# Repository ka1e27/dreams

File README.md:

# D.R.E.A.M.S

Autonomous survey catamaran: CV-based obstacle avoidance, environmental sensing, and cellular
telemetry to a web dashboard.

**Website:** https://ka1e27.github.io/dreams/ (the boat, the build log and weekly updates). Its source is in [`website/`](website/).
**Instagram:** [@dreams.boat.project](https://www.instagram.com/dreams.boat.project/).

## Status: V3, starting from scratch

V3 is a ground-up rebuild on new hardware. The carrier PCB is designed and fully routed. **None of
the software has been written yet.** This repo is the clean base it will be written on.

The V2 boat is archived, not deleted. The whole V2 stack is frozen at the tag
[`v2-final`](../../tree/v2-final): RP2040 firmware, the Pi 5 navigation and CV code, the
dashboards, the cloud pipeline, and the V2 board with its docs.

**Start with [`docs/v3/V3_DESIGN_BRIEF.md`](docs/v3/V3_DESIGN_BRIEF.md)** for the locked
decisions, the current budget, part choices with their reasons, and the layout traps the first
attempt hit.

## The boards

| Board | Folder | What it is |
|---|---|---|
| **V3 carrier** (rev F) | [`Boat_PCB/Boat_PCB_V3/`](Boat_PCB/Boat_PCB_V3/) | The main board: Pi 5 and two Pico 2s, running from 10S Li-ion. 122.1 × 95.5 mm, 4 layers (JLC04161H-7628, 1 oz outer / 0.5 oz inner, ENIG), 140 footprints, fully routed |
| **V3.1 starter carrier** (2026-10-10) | [`Boat_PCB/Boat_PCB_V3_1/`](Boat_PCB/Boat_PCB_V3_1/) | An interim board to get the boat moving before the full carrier. It keeps the Pi 5 and the 5 V buck, uses one Raspberry Pi Pico 2 instead of the full board's two, and runs from one 10S Li-ion pack. CAN chain for the VESCs, RC input, GPS, an on-board SHT41, a Qwiic port for the TMP119, hull leak probes, ESC headers and the pod tether, on a 98 × 67 mm 2-layer board. See [`docs/v3/V3_1_STARTER_CARRIER.md`](docs/v3/V3_1_STARTER_CARRIER.md) |
| **Pod** | [`Boat_PCB/Pod_PCB_V3/`](Boat_PCB/Pod_PCB_V3/) | A Seeed XIAO ESP32-S3 on its own board, on the winch tether |
| Shared library | [`Boat_PCB/lib/`](Boat_PCB/lib/) | The `dreams_v3` KiCad library all three boards use |

**Power on the V3 carrier (rev F):** two 10S 10 Ah Li-ion packs in parallel make one 10S bus.

- **Drive:** the 10S bus straight to the VESCs, off-board; the carrier only senses its voltage.
- **Electronics:** 10S → 5 V buck → Pi and both Picos. An optional 4S backup on J18 keeps that 5 V
  side up while the 10S bus is off. A 15 V regulator (U15) feeds the stepper driver and the pod.
- **Winch:** 10S → P-FET kill → ESC.

Pack fusing is off-board. On the board, PTCs guard the pod feed (F1) and the LED and SBUS 5 V
outputs (F2, F3).

## Architecture

```
Raspberry Pi 5 ─ navigation, mission logic, CV, cloud link        Python (not yet written)
  │ UART on the GPIO header to Pico A, plus a reset line to each Pico
  ├─ Pico A (Pico 2) ─ control                                    C++ (not yet written)
  │    ├─ CAN via TJA1051T/3 ─► VESC ×2 (node IDs 1, 2) for drive, on the PIO (can2040)
  │    ├─ UART ─────────────► SBUS RC receiver
  │    ├─ PWM ──────────────► winch ESC, behind a fail-safe-OFF high-side P-FET kill
  │    ├─ STEP/DIR ─────────► A4988 radar-bar stepper
  │    └─ GPIO / ADC ───────► WS2812 status LED · hull leak L/R · 10S pack divider
  └─ Pico B (Pico 2) ─ sensors                                    C++ (not yet written)
       ├─ I²C via TCA9548A ─► SHT45 ×2, BNO085, ADXL375, BH1750, INA228 ×2
       └─ UART ─────────────► GPS (M10-25Q) · pod tether (RS-485)
```

- **The Picos** sit in sockets under the carrier, with a UART link between them. They replaced the
  Teensy 4.1 in rev E (2026-10-13).
- **The Pi** talks to Pico A over a UART on its GPIO header, and Pico B reaches the Pi through Pico A.
  So USB cables are optional: without them the Pi's USB ports stay free for cameras and the modem;
  with them, either Pico can be flashed or run its link over USB instead.
- **The pod tether** carries one RS-485 pair and 15 V; the pod makes its own 5 V.

## Repo layout

```
Boat_PCB/Boat_PCB_V3/     KiCad 10 project: schematic and layout of the V3 carrier
Boat_PCB/Pod_PCB_V3/      the pod board (XIAO ESP32-S3 on the winch tether)
Boat_PCB/Boat_PCB_V3_1/   V3.1 starter carrier: Pi 5 + one Pico 2, an interim board
Boat_PCB/lib/             the dreams_v3 KiCad library all three boards share
Boat_PCB/CLAUDE.md        board baselines, layout constraints, ordering
docs/v3/                  design brief, planning record, BOM, V3.1 notes
website/                  the public site
CLAUDE.md                 working notes for Claude Code
```

## Checking a board

Open the project in KiCad 10, or check it from the command line:

```bash
kicad-cli sch erc --severity-all Boat_PCB/Boat_PCB_V3/Boat_PCB_V3.kicad_sch
kicad-cli pcb drc --severity-all --schematic-parity Boat_PCB/Boat_PCB_V3/Boat_PCB_V3.kicad_pcb
```

Each board's current numbers, and the layout rules to keep, are in
[`Boat_PCB/CLAUDE.md`](Boat_PCB/CLAUDE.md).

## What changed from V2

| | V2 (`v2-final`) | V3 |
|---|---|---|
| Boat MCU | RP2040 Pico, MicroPython | Two Pico 2s (RP2350), C++, a new pin map |
| Drive | Direct servo PWM to AM32/BLHeli ESCs | VESCs as CAN nodes via TJA1051 |
| Packs | Milwaukee M18 | Two 10S 10 Ah Li-ion in parallel, one bus; optional 4S backup for the 5 V side |
| Pod | RP2040 Pico | XIAO ESP32-S3 on its own board |
| Sensors | SHT41 ×2, BNO085 | SHT45 ×2, BNO085, ADXL375, BH1750, INA228 ×2, behind a mux |

V3 contradicts V2 on purpose. Don't try to reconcile the two. See
[`docs/v3/README.md`](docs/v3/README.md) for the full table.

## Sponsors

[PCBWay](https://www.pcbway.com/) sponsors the project's circuit boards.

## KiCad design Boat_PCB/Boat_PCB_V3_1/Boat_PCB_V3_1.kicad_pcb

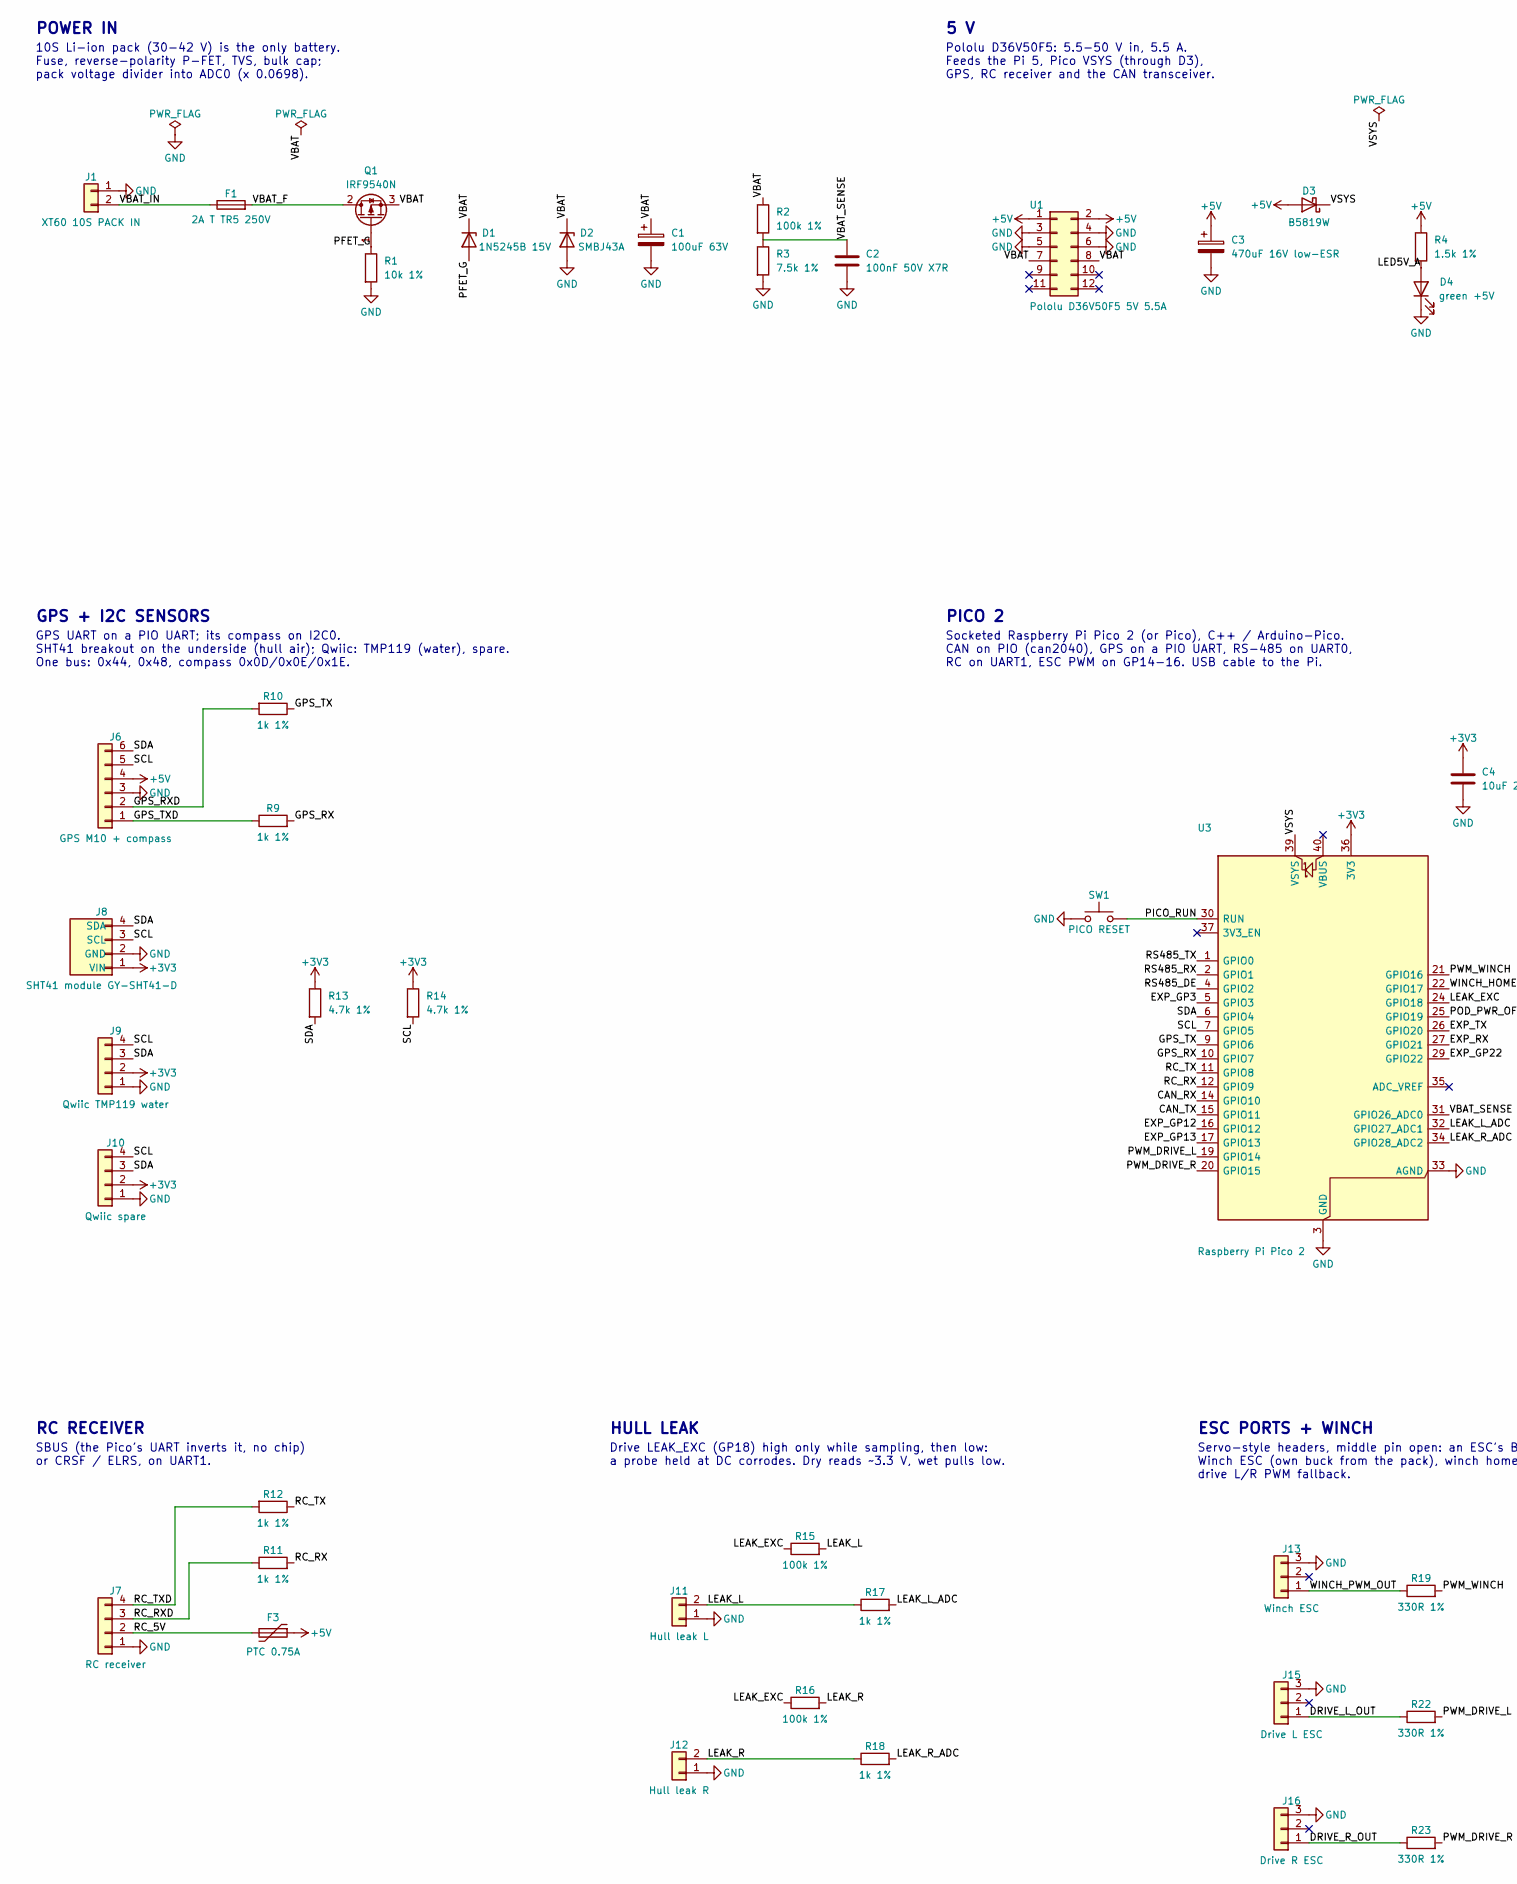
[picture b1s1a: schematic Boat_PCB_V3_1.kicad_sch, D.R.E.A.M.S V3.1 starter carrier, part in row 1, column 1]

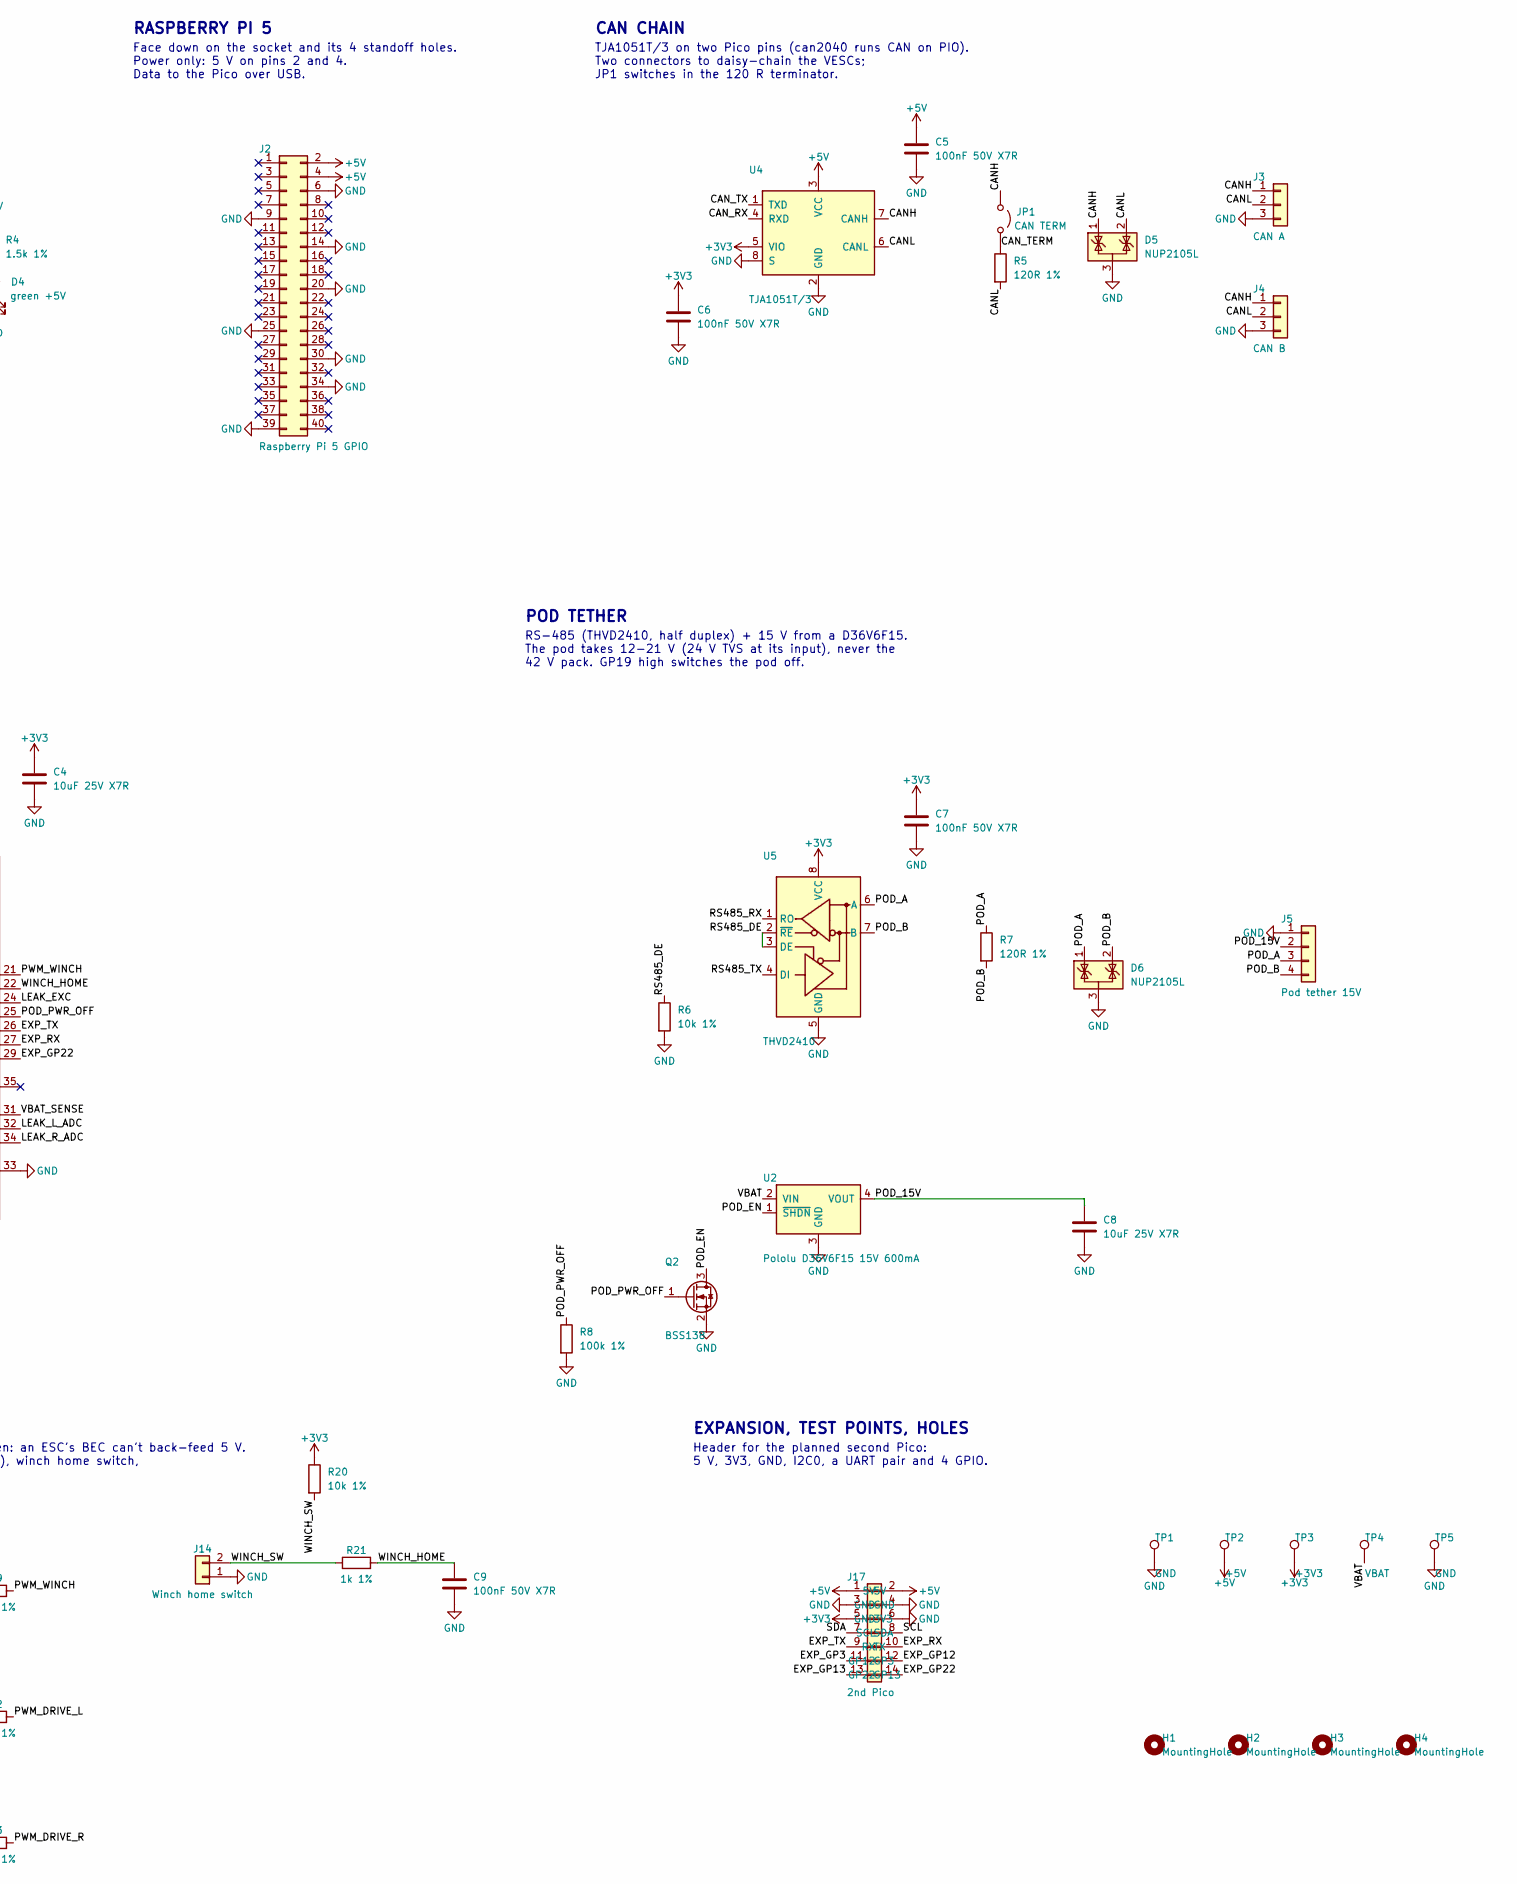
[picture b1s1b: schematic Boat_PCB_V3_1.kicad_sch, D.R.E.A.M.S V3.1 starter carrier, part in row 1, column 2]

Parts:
C1: 100uF 63V; CP_Radial_D10.0mm_P5.00mm
C2, C5, C6, C7, C9: 100nF 50V X7R; C_Disc_D5.0mm_W2.5mm_P5.00mm
C3: 470uF 16V low-ESR; CP_Radial_D8.0mm_P3.50mm
C4, C8: 10uF 25V X7R; C_Disc_D5.0mm_W2.5mm_P5.00mm
D1: 1N5245B 15V; D_DO-35_SOD27_P7.62mm_Horizontal
D2: SMBJ43A; D_SMB
D3: B5819W; D_SOD-123
D4: green +5V; LED_D3.0mm
D5, D6: NUP2105L; SOT-23
F1: 2A T TR5 250V; Fuse_Littelfuse_372_D8.50mm
F3: PTC 0.75A; Fuse_BelFuse_0ZRE0075FF_L11.5mm_W4.8mm
H1, H2, H3, H4: MountingHole; MountingHole_3.2mm_M3
J1: XT60 10S PACK IN; AMASS_XT60-M_1x02_P7.20mm_Vertical
J2: Raspberry Pi 5 GPIO; RaspberryPi_5_GPIO_Socket_2x20
J3: CAN A; JST_XH_B3B-XH-A_1x03_P2.50mm_Vertical
J4: CAN B; JST_XH_B3B-XH-A_1x03_P2.50mm_Vertical
J5: Pod tether 15V; JST_XH_B4B-XH-A_1x04_P2.50mm_Vertical
J6: GPS M10 + compass; JST_XH_B6B-XH-A_1x06_P2.50mm_Vertical
J7: RC receiver; JST_XH_B4B-XH-A_1x04_P2.50mm_Vertical
J8: SHT41 module GY-SHT41-D; SHT41_Module_GY-SHT41-D_1x04_P2.54mm
J9: Qwiic TMP119 water; JST_SH_SM04B-SRSS-TB_1x04-1MP_P1.00mm_Horizontal
J10: Qwiic spare; JST_SH_SM04B-SRSS-TB_1x04-1MP_P1.00mm_Horizontal
J11: Hull leak L; JST_XH_B2B-XH-A_1x02_P2.50mm_Vertical
J12: Hull leak R; JST_XH_B2B-XH-A_1x02_P2.50mm_Vertical
J13: Winch ESC; PinHeader_1x03_P2.54mm_Vertical
J14: Winch home switch; JST_XH_B2B-XH-A_1x02_P2.50mm_Vertical
J15: Drive L ESC; PinHeader_1x03_P2.54mm_Vertical
J16: Drive R ESC; PinHeader_1x03_P2.54mm_Vertical
J17: 2nd Pico; PinHeader_2x07_P2.54mm_Vertical
JP1: CAN TERM; PinHeader_1x02_P2.54mm_Vertical
Q1: IRF9540N; TO-220-3_Vertical
Q2: BSS138; SOT-23
R1, R6, R20: 10k 1%; R_Axial_DIN0207_L6.3mm_D2.5mm_P10.16mm_Horizontal
R2, R8, R15, R16: 100k 1%; R_Axial_DIN0207_L6.3mm_D2.5mm_P10.16mm_Horizontal
R3: 7.5k 1%; R_Axial_DIN0207_L6.3mm_D2.5mm_P10.16mm_Horizontal
R4: 1.5k 1%; R_Axial_DIN0207_L6.3mm_D2.5mm_P10.16mm_Horizontal
R5, R7: 120R 1%; R_Axial_DIN0207_L6.3mm_D2.5mm_P10.16mm_Horizontal
R9, R10, R11, R12, R17, R18, R21: 1k 1%; R_Axial_DIN0207_L6.3mm_D2.5mm_P10.16mm_Horizontal
R13, R14: 4.7k 1%; R_Axial_DIN0207_L6.3mm_D2.5mm_P10.16mm_Horizontal
R19, R22, R23: 330R 1%; R_Axial_DIN0207_L6.3mm_D2.5mm_P10.16mm_Horizontal
SW1: PICO RESET; SW_PUSH_6mm
TP1, TP5: GND; TestPoint_Keystone_5000-5004_Miniature
TP2: +5V; TestPoint_Keystone_5000-5004_Miniature
TP3: +3V3; TestPoint_Keystone_5000-5004_Miniature
TP4: VBAT; TestPoint_Keystone_5000-5004_Miniature
U1: Pololu D36V50F5 5V 5.5A; Pololu_D36V50F5
U2: Pololu D36V6F15 15V 600mA; Pololu_D36V6F5
U3: Raspberry Pi Pico 2; RaspberryPi_Pico_Socketed_THT
U4: TJA1051T/3; SOIC-8_3.9x4.9mm_P1.27mm
U5: THVD2410; SOIC-8_3.9x4.9mm_P1.27mm

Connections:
+3V3: C4.1, C6.1, C7.1, J8.1 (VIN), J9.2 (3V3), J10.2 (3V3), J17.5 (3V3), R13.1, R14.1, R20.1, TP3.1, U3.36 (3V3), U4.5 (VIO), U5.8 (VCC)
+5V: C3.1, C5.1, D3.2 (A), F3.1, J2.2 (5V), J2.4 (5V), J6.4 (V), J17.1 (5V), J17.2 (5V), R4.1, TP2.1, U1.1 (VOUT), U1.2 (VOUT), U4.3 (VCC)
/CANH: D5.1 (K), J3.1 (CANH), J4.1 (CANH), JP1.1 (A), U4.7 (CANH)
/CANL: D5.2 (K), J3.2 (CANL), J4.2 (CANL), R5.2, U4.6 (CANL)
/CAN_RX: U3.14 (GPIO10), U4.4 (RXD)
/CAN_TERM: JP1.2 (B), R5.1
/CAN_TX: U3.15 (GPIO11), U4.1 (TXD)
/DRIVE_L_OUT: J15.1 (SIG), R22.1
/DRIVE_R_OUT: J16.1 (SIG), R23.1
/EXP_GP3: J17.11 (GP3), U3.5 (GPIO3)
/EXP_GP12: J17.12 (GP12), U3.16 (GPIO12)
/EXP_GP13: J17.13 (GP13), U3.17 (GPIO13)
/EXP_GP22: J17.14 (GP22), U3.29 (GPIO22)
/EXP_RX: J17.10 (RX), U3.27 (GPIO21)
/EXP_TX: J17.9 (TX), U3.26 (GPIO20)
/GPS_RX: R9.2, U3.10 (GPIO7)
/GPS_RXD: J6.2 (RX), R10.2
/GPS_TX: R10.1, U3.9 (GPIO6)
/GPS_TXD: J6.1 (TX), R9.1
/LEAK_EXC: R15.1, R16.1, U3.24 (GPIO18)
/LEAK_L: J11.2 (LEAK), R15.2, R17.1
/LEAK_L_ADC: R17.2, U3.32 (GPIO27_ADC1)
/LEAK_R: J12.2 (LEAK), R16.2, R18.1
/LEAK_R_ADC: R18.2, U3.34 (GPIO28_ADC2)
/LED5V_A: D4.2 (A), R4.2
/PFET_G: D1.2 (A), Q1.1 (G), R1.1
/PICO_RUN: SW1.2, U3.30 (RUN)
/POD_15V: C8.1, J5.2 (VPACK), U2.4 (VOUT)
/POD_A: D6.1 (K), J5.3 (A), R7.1, U5.6 (A)
/POD_B: D6.2 (K), J5.4 (B), R7.2, U5.7 (B)
/POD_EN: Q2.3 (D), U2.1 (~SHDN)
/POD_PWR_OFF: Q2.1 (G), R8.1, U3.25 (GPIO19)
/PWM_DRIVE_L: R22.2, U3.19 (GPIO14)
/PWM_DRIVE_R: R23.2, U3.20 (GPIO15)
/PWM_WINCH: R19.2, U3.21 (GPIO16)
/RC_5V: F3.2, J7.2 (5V)
/RC_RX: R11.2, U3.12 (GPIO9)
/RC_RXD: J7.3 (RX), R11.1
/RC_TX: R12.1, U3.11 (GPIO8)
/RC_TXD: J7.4 (TX), R12.2
/RS485_DE: R6.1, U3.4 (GPIO2), U5.2 (~RE), U5.3 (DE)
/RS485_RX: U3.2 (GPIO1), U5.1 (RO)
/RS485_TX: U3.1 (GPIO0), U5.4 (DI)
/SCL: J6.5 (SCL), J8.3 (SCL), J9.4 (SCL), J10.4 (SCL), J17.8 (SCL), R14.2, U3.7 (GPIO5)
/SDA: J6.6 (SDA), J8.4 (SDA), J9.3 (SDA), J10.3 (SDA), J17.7 (SDA), R13.2, U3.6 (GPIO4)
/VBAT: C1.1, D1.1 (K), D2.1 (K), Q1.3 (S), R2.1, TP4.1, U1.7 (VIN), U1.8 (VIN), U2.2 (VIN)
/VBAT_F: F1.2, Q1.2 (D)
/VBAT_IN: F1.1, J1.2 (+)
/VBAT_SENSE: C2.1, R2.2, R3.1, U3.31 (GPIO26_ADC0)
/VSYS: D3.1 (K), U3.39 (VSYS)
/WINCH_HOME: C9.1, R21.2, U3.22 (GPIO17)
/WINCH_PWM_OUT: J13.1 (SIG), R19.1
/WINCH_SW: J14.2 (SW), R20.2, R21.1
GND: C1.2, C2.2, C3.2, C4.2, C5.2, C6.2, C7.2, C8.2, C9.2, D2.2 (A), D4.1 (K), D5.3 (A), D6.3 (A), J1.1 (-), J2.6 (GND), J2.9 (GND), J2.14 (GND), J2.20 (GND), J2.25 (GND), J2.30 (GND), J2.34 (GND), J2.39 (GND), J3.3 (GND), J4.3 (GND), J5.1 (GND), J6.3 (GND), J7.1 (GND), J8.2 (GND), J9.1 (GND), J10.1 (GND), J11.1 (GND), J12.1 (GND), J13.3 (GND), J14.1 (GND), J15.3 (GND), J16.3 (GND), J17.3 (GND), J17.4 (GND), J17.6 (GND), Q2.2 (S), R1.2, R3.2, R6.2, R8.2, SW1.1, TP1.1, TP5.1, U1.3 (GND), U1.4 (GND), U1.5 (GND), U1.6 (GND), U2.3 (GND), U3.3 (GND), U3.8 (GND), U3.13 (GND), U3.18 (GND), U3.23 (GND), U3.28 (GND), U3.33 (AGND), U3.38 (GND), U4.2 (GND), U4.8 (S), U5.5 (GND)

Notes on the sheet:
POWER IN
10S Li-ion pack (30-42 V) is the only battery. Fuse, reverse-polarity P-FET, TVS, bulk cap; pack voltage divider into ADC0 (x 0.0698).
5 V
Pololu D36V50F5: 5.5-50 V in, 5.5 A. Feeds the Pi 5, Pico VSYS (through D3), GPS, RC receiver and the CAN transceiver.
RASPBERRY PI 5
Face down on the socket and its 4 standoff holes. Power only: 5 V on pins 2 and 4. Data to the Pico over USB.
CAN CHAIN
TJA1051T/3 on two Pico pins (can2040 runs CAN on PIO). Two connectors to daisy-chain the VESCs; JP1 switches in the 120 R terminator.
PICO 2
Socketed Raspberry Pi Pico 2 (or Pico), C++ / Arduino-Pico. CAN on PIO (can2040), GPS on a PIO UART, RS-485 on UART0, RC on UART1, ESC PWM on GP14-16. USB cable to the Pi.
GPS + I2C SENSORS
GPS UART on a PIO UART; its compass on I2C0. SHT41 breakout on the underside (hull air); Qwiic: TMP119 (water), spare. One bus: 0x44, 0x48, compass 0x0D/0x0E/0x1E.
POD TETHER
RS-485 (THVD2410, half duplex) + 15 V from a D36V6F15. The pod takes 12-21 V (24 V TVS at its input), never the 42 V pack. GP19 high switches the pod off.
RC RECEIVER
SBUS (the Pico's UART inverts it, no chip) or CRSF / ELRS, on UART1.
HULL LEAK
Drive LEAK_EXC (GP18) high only while sampling, then low: a probe held at DC corrodes. Dry reads ~3.3 V, wet pulls low.
ESC PORTS + WINCH
Servo-style headers, middle pin open: an ESC's BEC can't back-feed 5 V. Winch ESC (own buck from the pack), winch home switch, drive L/R PWM fallback.
EXPANSION, TEST POINTS, HOLES
Header for the planned second Pico: 5 V, 3V3, GND, I2C0, a UART pair and 4 GPIO.

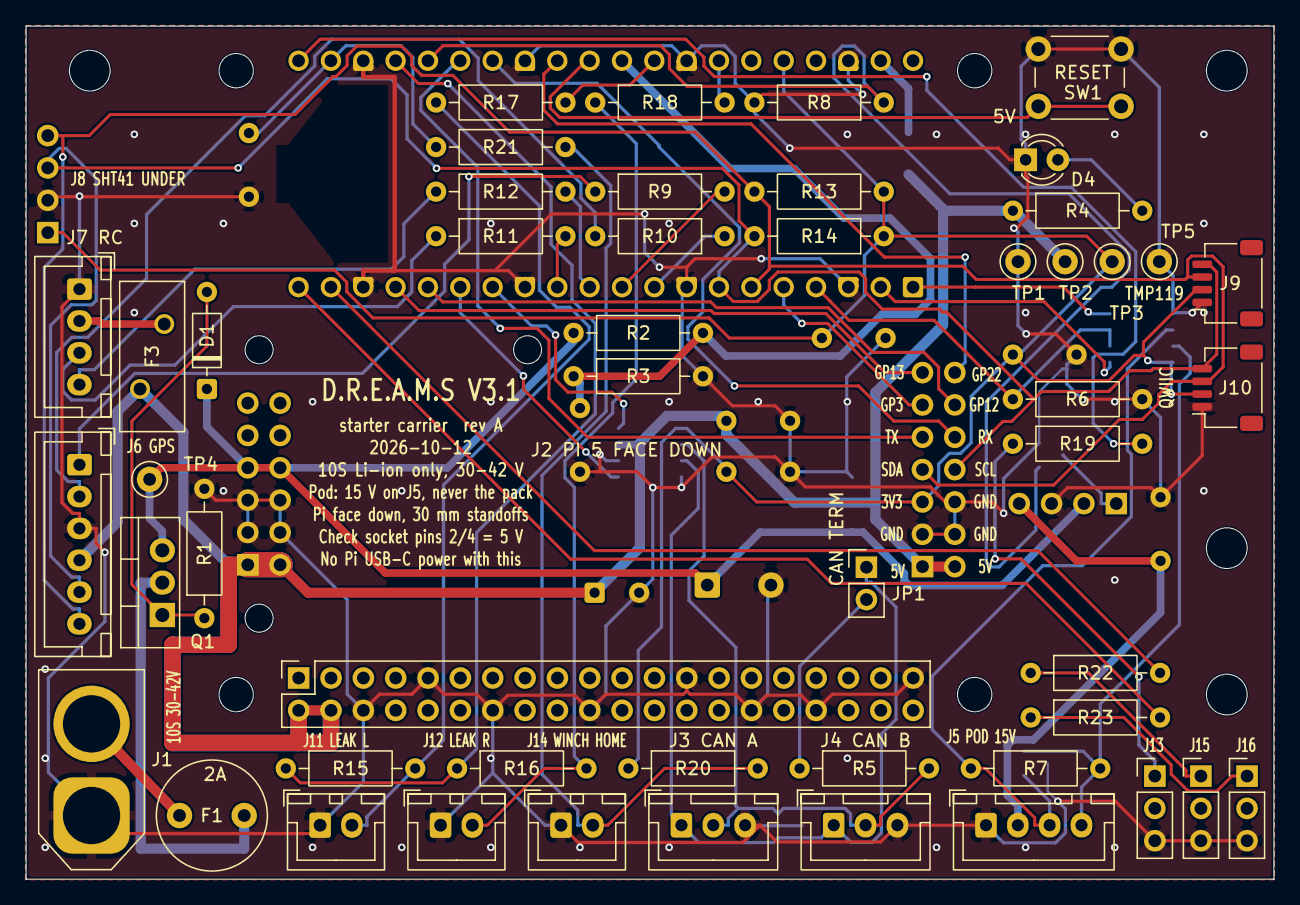
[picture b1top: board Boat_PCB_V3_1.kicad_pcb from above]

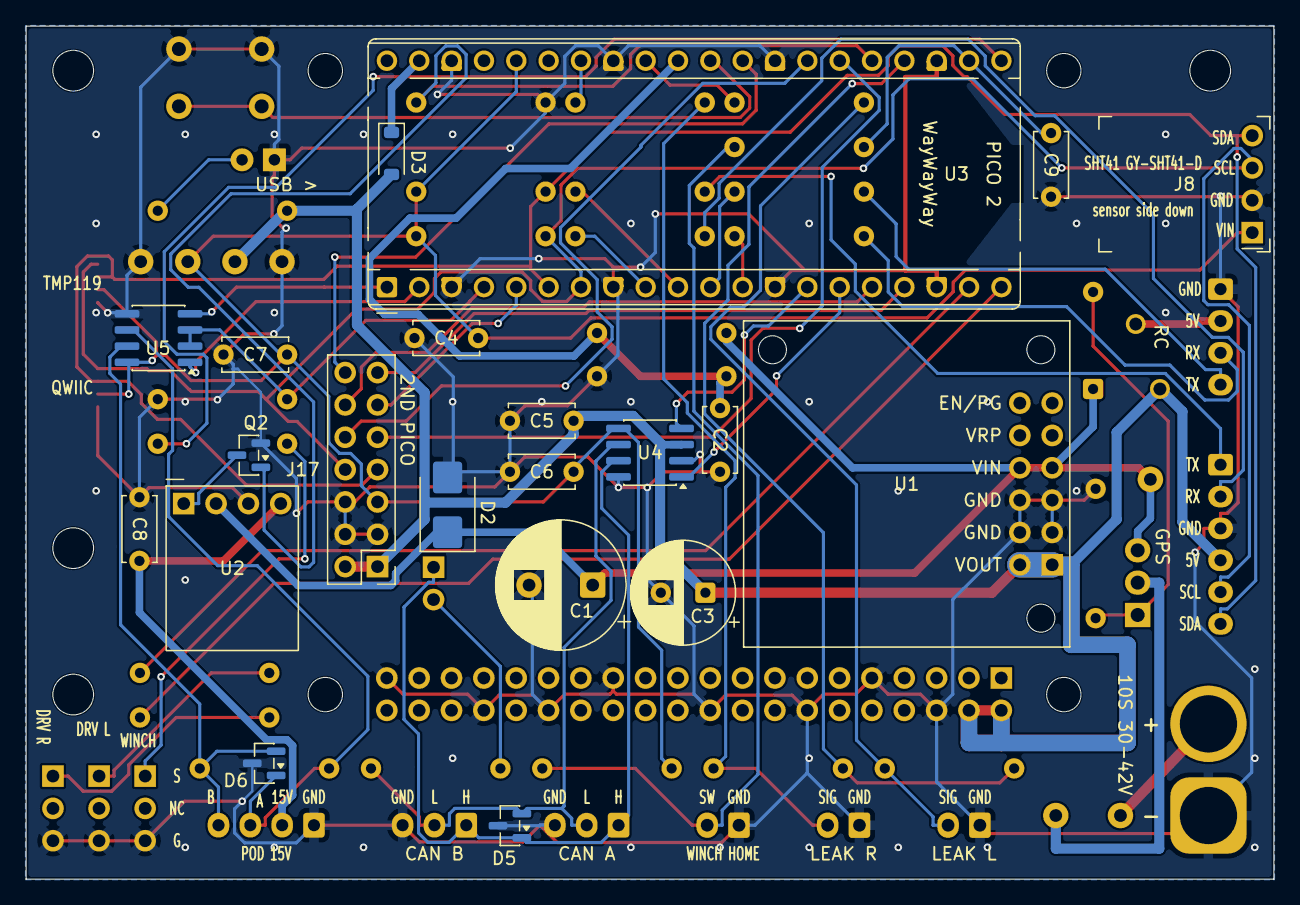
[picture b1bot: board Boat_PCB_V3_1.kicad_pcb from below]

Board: 2 copper layers, 98.0 x 67.0 mm, 75 parts (21 on the bottom side), 54 nets.

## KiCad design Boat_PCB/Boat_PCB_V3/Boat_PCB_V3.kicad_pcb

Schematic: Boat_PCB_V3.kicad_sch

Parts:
A1: A4988 radar stepper; Pololu_Breakout-16_15.2x20.3mm
A2: Pololu D36V50F5 5V 5.5A; Pololu_D36V50F5
C1, C2, C26: 100uF 63V; CP_Radial_D10.0mm_P5.00mm
C4, C9, C11, C12, C13, C14, C15, C16, C17, C18, C20, C21, C22, C31, C32, C34: 100nF 50V X7R; C_Disc_D5.0mm_W2.5mm_P5.00mm
C24: 10uF 25V X7R; C_Disc_D5.0mm_W2.5mm_P5.00mm
C25: 470uF 35V; CP_Radial_D10.0mm_P5.00mm
C28, C29: 22pF 50V C0G; C_Disc_D3.0mm_W1.6mm_P2.50mm
C30: 470uF 16V low-ESR 105C; CP_Radial_D8.0mm_P3.50mm
C33: 1uF 50V X7R; C_Disc_D5.0mm_W2.5mm_P5.00mm
D2: 1N5245B 15V; D_DO-35_SOD27_P7.62mm_Horizontal
D3, D4: SMBJ43A; D_SMB
D5: SMBJ5.0A; D_SMB
D6: NUP2105L; SOT-23
D7: green +5V; LED_D3.0mm
D8: green +3V3; LED_D3.0mm
D9: red WINCH ON; LED_D3.0mm
D10, D11: B5819W; D_SOD-123
D12, D13: B360B; D_SMB
F1: PTC 0.40A hold; Fuse_BelFuse_0ZRE0075FF_L11.5mm_W4.8mm
F2: PTC 1.25A hold; Fuse_BelFuse_0ZRE0125FF_L21.2mm_W5.3mm
F3: PTC 0.75A hold; Fuse_BelFuse_0ZRE0075FF_L11.5mm_W4.8mm
J1: GPS M10-25Q; JST_XH_B6B-XH-A_1x06_P2.50mm_Vertical
J2: Pod tether; JST_XH_B4B-XH-A_1x04_P2.50mm_Vertical
J3: CAN stub to VESCs; JST_XH_B3B-XH-A_1x03_P2.50mm_Vertical
J4: SHT45 external; JST_XH_B4B-XH-A_1x04_P2.50mm_Vertical
J5: Radar stepper motor; JST_XH_B4B-XH-A_1x04_P2.50mm_Vertical
J6: Status LED; JST_XH_B3B-XH-A_1x03_P2.50mm_Vertical
J7: SBUS RC receiver; JST_XH_B3B-XH-A_1x03_P2.50mm_Vertical
J8: Hull leak left; JST_XH_B2B-XH-A_1x02_P2.50mm_Vertical
J9: Hull leak right; JST_XH_B2B-XH-A_1x02_P2.50mm_Vertical
J10: Winch ESC; JST_XH_B2B-XH-A_1x02_P2.50mm_Vertical
J11: 10S pack tap (JST-VH); JST_VH_B2P-VH_1x02_P3.96mm_Vertical
J12: Raspberry Pi 5 GPIO; RaspberryPi_5_GPIO_Socket_2x20
J13: XT60 10S ELECTRONICS; AMASS_XT60-M_1x02_P7.20mm_Vertical
J14: XT60 10S WINCH; AMASS_XT60-M_1x02_P7.20mm_Vertical
J16: XT60-F WINCH ESC OUT (female); AMASS_XT60-F_1x02_P7.20mm_Vertical
J18: 4S backup (JST-VH); JST_VH_B2P-VH_1x02_P3.96mm_Vertical
JP1: CAN TERM; PinHeader_1x02_P2.54mm_Vertical
MH1, MH2, MH3, MH4: MountingHole; MountingHole_3.2mm_M3
Q1: SUP90P06-09L; TO-220-3_Vertical
Q2, Q3, Q4: BSS138; SOT-23
R7: 220k 1%; R_Axial_DIN0207_L6.3mm_D2.5mm_P10.16mm_Horizontal
R8: 13k 1%; R_Axial_DIN0207_L6.3mm_D2.5mm_P10.16mm_Horizontal
R9, R10, R15, R16, R17, R18, R21, R22, R23, R24, R25, R26, R27, R28, R29, R30, R31, R36, R62: 4.7k 1%; R_Axial_DIN0207_L6.3mm_D2.5mm_P10.16mm_Horizontal
R32: 10mR 1%; R_Shunt_Vishay_WSK2512_6332Metric_T1.19mm
R33: 2mR 1%; R_Shunt_Vishay_WSK2512_6332Metric_T1.19mm
R34, R35, R38, R39, R40, R42, R43, R44, R55: 10k 1%; R_Axial_DIN0207_L6.3mm_D2.5mm_P10.16mm_Horizontal
R45: 330R 1%; R_Axial_DIN0207_L6.3mm_D2.5mm_P10.16mm_Horizontal
R46, R47, R48, R49, R50, R53: 1k 1%; R_Axial_DIN0207_L6.3mm_D2.5mm_P10.16mm_Horizontal
R54, R56, R57, R64, R65: 100k 1%; R_Axial_DIN0207_L6.3mm_D2.5mm_P10.16mm_Horizontal
R58: 1.5k 1%; R_Axial_DIN0207_L6.3mm_D2.5mm_P10.16mm_Horizontal
R59: 680R 1%; R_Axial_DIN0207_L6.3mm_D2.5mm_P10.16mm_Horizontal
R60: 22k 1%; R_Axial_DIN0207_L6.3mm_D2.5mm_P10.16mm_Horizontal
R61, R63: 120R 1%; R_Axial_DIN0207_L6.3mm_D2.5mm_P10.16mm_Horizontal
R66, R67: 1k 1%; R_Axial_DIN0207_L6.3mm_D2.5mm_P2.54mm_Vertical
SW1: PICO A RESET; SW_PUSH_6mm
SW2: PICO B RESET; SW_PUSH_6mm
TP1, TP2: GND; TestPoint_Keystone_5000-5004_Miniature
TP3: +5V; TestPoint_Keystone_5000-5004_Miniature
TP4: +3V3; TestPoint_Keystone_5000-5004_Miniature
TP5: SDA; TestPoint_Keystone_5000-5004_Miniature
TP6: SCL; TestPoint_Keystone_5000-5004_Miniature
U1, U14: Raspberry Pi Pico 2; RaspberryPi_Pico_Socketed_THT
U2: TCA9548A I2C mux; TSSOP-24_4.4x7.8mm_P0.65mm
U3: TJA1051T/3 CAN xcvr; SOIC-8_3.9x4.9mm_P1.27mm
U4: BNO085; LGA-28_5.2x3.8mm_P0.5mm
U5: ADXL375; LGA-14_3x5mm_P0.8mm_LayoutBorder1x6y
U7: BH1750FVI-TR; XDCR_BH1750FVI-TR
U8: SHT45 internal; Sensirion_DFN-4_1.5x1.5mm_P0.8mm_SHT4x_NoCentralPad
U10: INA228 electronics; MSOP-10_3x3mm_P0.5mm
U11: INA228 winch; MSOP-10_3x3mm_P0.5mm
U12: 74AHCT1G125; SOT-23-5
U13: THVD2410; SOIC-8_3.9x4.9mm_P1.27mm
U15: Pololu D36V6F15 15V 600mA; Pololu_D36V6F5
Y1: 32.768kHz CL=12.5pF 50ppm; Crystal_SMD_3215-2Pin_3.2x1.5mm

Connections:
/+15V: A1.8 (VMOT), C25.1, F1.1, U15.4 (VOUT)
/+VBACKUP: D13.2 (A), J18.2 (VIN)
/+VELEC: C1.1, D3.1 (K), D12.2 (A), R32.4, U15.2 (VIN)
/+VLOGIC: A2.7 (VIN), A2.8 (VIN), D12.1 (K), D13.1 (K)
/+VWINCH: C2.1, D2.1 (K), Q1.3 (S), R33.4, R34.1
/ADXL_INT1: U5.8 (INT1), U14.25 (GPIO19)
/ADXL_INT2: U5.9 (INT2), U14.26 (GPIO20)
/BH_ADDR: R54.1, U7.2 (ADDR)
/CANH: J3.1 (CANH), R61.1, U3.7 (CANH)
/CANL: J3.2 (CANL), JP1.2 (B), U3.6 (CANL)
/CAN_RX: U1.19 (GPIO14), U3.4 (RXD)
/CAN_TERM: JP1.1 (A), R61.2
/CAN_TX: U1.20 (GPIO15), U3.1 (TXD)
/CH0_SCL: R16.2, U2.5 (SC0), U4.19 (H_SCL/SCK/RX)
/CH0_SDA: R15.2, U2.4 (SD0), U4.20 (H_SDA/H_MISO/TX)
/CH1_SCL: R18.2, U2.7 (SC1), U5.14 (SCL/SCLK)
/CH1_SDA: R17.2, U2.6 (SD1), U5.13 (SDA/SDI/SDIO)
/CH3_SCL: R22.2, U2.11 (SC3), U7.6 (SCL)
/CH3_SDA: R21.2, U2.10 (SD3), U7.4 (SDA)
/CH4_SCL: R24.2, U2.14 (SC4), U8.2 (SCL)
/CH4_SDA: R23.2, U2.13 (SD4), U8.1 (SDA)
/CH5_SCL: J4.4 (SCL), R26.2, U2.16 (SC5)
/CH5_SDA: J4.3 (SDA), R25.2, U2.15 (SD5)
/CH6_SCL: R28.2, U2.18 (SC6), U10.5 (SCL), U11.5 (SCL)
/CH6_SDA: R27.2, U2.17 (SD6), U10.4 (SDA), U11.4 (SDA)
/CH7_SCL: J1.5 (SCL), R30.2, U2.20 (SC7)
/CH7_SDA: J1.6 (SDA), R29.2, U2.19 (SD7)
/ELEC_SHUNT_N: R32.3, U10.8 (Vbus), U10.9 (Vin-)
/ELEC_SHUNT_P: R32.2, U10.10 (Vin+)
/ENV_SCL: R43.2, U4.15 (ENV_SCL)
/ENV_SDA: R44.2, U4.16 (ENV_SDA)
/GPS_RX: R50.1, U14.6 (GPIO4)
/GPS_RX_EXT: J1.2 (RX), R50.2
/GPS_TX: R49.2, U14.7 (GPIO5)
/GPS_TX_EXT: J1.1 (TX), R49.1
/I2C_SCL: R10.2, TP6.1, U2.22 (SCL), U14.17 (GPIO13)
/I2C_SDA: R9.2, TP5.1, U2.23 (SDA), U14.16 (GPIO12)
/IMU_BOOTN: R55.2, U4.4 (~BOOT)
/IMU_CAP: C13.1, U4.9 (CAP)
/IMU_INT: U4.14 (~H_INT), U14.11 (GPIO8)
/IMU_RST: R39.2, U4.11 (~RST), U14.12 (GPIO9)
/IMU_XIN: C28.1, U4.27 (XIN32), Y1.1
/IMU_XOUT: C29.1, U4.26 (XOUT32/CLKSEL1), Y1.2
/INA_ALERT: R31.2, U10.3 (~Alert), U11.3 (~Alert), U14.10 (GPIO7)
/LEAK_EXC: R56.1, R57.1, U1.29 (GPIO22)
/LEAK_L: R46.1, R56.2, U1.32 (GPIO27_ADC1)
/LEAK_L_EXT: J8.2 (LEAK), R46.2
/LEAK_R: R47.1, R57.2, U1.34 (GPIO28_ADC2)
/LEAK_R_EXT: J9.2 (LEAK), R47.2
/LED_5V: F2.2, J6.2 (5V)
/LED_DIN: U1.14 (GPIO10), U12.2
/LED_DIN_5V: R45.1, U12.4
/LED_DIN_EXT: J6.3 (DIN), R45.2
/LED_P3V3: D8.2 (A), R59.2
/LED_P5V: D7.2 (A), R58.2
/LED_WINCH: D9.2 (A), R60.2
/LINK_A2B: U1.26 (GPIO20), U14.15 (GPIO11)
/LINK_B2A: U1.27 (GPIO21), U14.14 (GPIO10)
/MUX_RST: R38.2, U2.3 (~RESET), U14.19 (GPIO14)
/PACK_ADC: C4.1, R7.2, R8.1, U1.31 (GPIO26_ADC0)
/PACK_RAW: J11.2 (VIN), R7.1
/PICO_A_RUN: Q3.3 (D), SW1.2, U1.30 (RUN)
/PICO_A_RX: R66.2, U1.22 (GPIO17)
/PICO_A_TX: R67.2, U1.21 (GPIO16)
/PICO_A_VSYS: D10.1 (K), U1.39 (VSYS)
/PICO_B_RUN: Q4.3 (D), SW2.2, U14.30 (RUN)
/PICO_B_VSYS: D11.1 (K), U14.39 (VSYS)
/PI_RST_A: J12.16 (GPIO23), Q3.1 (G), R64.1
/PI_RST_B: J12.18 (GPIO24), Q4.1 (G), R65.1
/PI_RX: J12.10 (GPIO15_RXD), R67.1
/PI_TX: J12.8 (GPIO14_TXD), R66.1
/POD_15V: F1.2, J2.2 (VPACK)
/PWR_GOOD: A2.12 (PG), R42.2, U1.15 (GPIO11)
/SBUS: R48.1, U1.2 (GPIO1)
/SBUS_5V: F3.2, J7.2 (5V)
/SBUS_EXT: J7.3 (SBUS), R48.2
/SH_ELEC_P: J13.2 (+), R32.1
/SH_WINCH_P: J14.2 (+), R33.1
/STEP: A1.15 (STEP), U1.5 (GPIO3)
/STEP_DIR: A1.16 (DIR), U1.4 (GPIO2)
/STEP_EN: A1.9 (~ENABLE), R40.2, U1.11 (GPIO8)
/STEP_MS1: A1.10 (MS1), U1.10 (GPIO7)
/STEP_MS2: A1.11 (MS2), U1.9 (GPIO6)
/STEP_MS3: A1.12 (MS3), U1.7 (GPIO5)
/STEP_SLEEP: A1.14 (~SLEEP), U1.6 (GPIO4)
/ST_1A: A1.4 (1A), J5.1 (1A)
/ST_1B: A1.3 (1B), J5.2 (1B)
/ST_2A: A1.5 (2A), J5.3 (2A)
/ST_2B: A1.6 (2B), J5.4 (2B)
/TETHER_A: D6.1 (K), J2.3 (A), R63.1, U13.6 (A)
/TETHER_B: D6.2 (K), J2.4 (B), R63.2, U13.7 (B)
/TETHER_DE: R62.1, U13.2 (~RE), U13.3 (DE), U14.24 (GPIO18)
/TETHER_RX: U13.1 (RO), U14.22 (GPIO17)
/TETHER_TX: U13.4 (DI), U14.21 (GPIO16)
/WINCH_GATE: D2.2 (A), Q1.1 (G), R34.2, R35.1
/WINCH_GDRV: Q2.3 (D), R35.2
/WINCH_KILL: Q2.1 (G), R36.1, U1.12 (GPIO9)
/WINCH_PWM: R53.1, U1.1 (GPIO0)
/WINCH_PWM_EXT: J10.2 (PWM), R53.2
/WINCH_SHUNT_N: R33.3, U11.8 (Vbus), U11.9 (Vin-)
/WINCH_SHUNT_P: R33.2, U11.10 (Vin+)
/WINCH_SW: C26.1, D4.1 (K), J16.2 (+), Q1.2 (D), R60.1
GND: A1.1 (GND), A1.7 (GND), A2.3 (GND), A2.4 (GND), A2.5 (GND), A2.6 (GND), C1.2, C2.2, C4.2, C9.2, C11.2, C12.2, C13.2, C14.2, C15.2, C16.2, C17.2, C18.2, C20.2, C21.2, C22.2, C24.2, C25.2, C26.2, C28.2, C29.2, C30.2, C31.2, C32.2, C33.2, C34.2, D3.2 (A), D4.2 (A), D5.2 (A), D6.3 (A), D7.1 (K), D8.1 (K), D9.1 (K), J1.3 (GND), J2.1 (GND), J3.3 (GND), J4.1 (GND), J6.1 (GND), J7.1 (GND), J8.1 (GND), J9.1 (GND), J10.1 (GND), J11.1 (GND), J12.6 (GND), J12.9 (GND), J12.14 (GND), J12.20 (GND), J12.25 (GND), J12.30 (GND), J12.34 (GND), J12.39 (GND), J13.1 (-), J14.1 (-), J16.1 (-), J18.1 (GND), Q2.2 (S), Q3.2 (S), Q4.2 (S), R8.2, R36.2, R54.2, R62.2, R64.2, R65.2, SW1.1, SW2.1, TP1.1, TP2.1, U1.3 (GND), U1.8 (GND), U1.13 (GND), U1.18 (GND), U1.23 (GND), U1.28 (GND), U1.33 (AGND), U1.38 (GND), U2.1 (A0), U2.2 (A1), U2.12 (GND), U2.21 (A2), U3.2 (GND), U3.8 (S), U4.2 (GND), U4.5 (PS1), U4.6 (PS0/WAKE), U4.10 (CLKSEL0), U4.17 (SA0/H_MOSI), U4.25 (GNDIO), U5.2 (GND), U5.4 (GND), U5.5 (GND), U5.11 (RES), U5.12 (SDO/ADDR), U7.3 (GND), U8.4 (VSS), U10.1 (A1), U10.7 (GND), U11.2 (A0), U11.7 (GND), U12.1, U12.3 (GND), U13.5 (GND), U14.3 (GND), U14.8 (GND), U14.13 (GND), U14.18 (GND), U14.23 (GND), U14.28 (GND), U14.33 (AGND), U14.38 (GND), U15.3 (GND)

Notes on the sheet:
CARRIER - COMPUTE & BUS
CARRIER - ON-BOARD SENSORS
CARRIER - CURRENT SENSE (electronics and winch feeds only; the drive is voltage-only, and the VESCs already report per-motor current over CAN)
BATTERY SENSE - 10S pack tap J11, 220k/13k = 17.9x (2.34 V at 42 V, room up to 12S), plus C4 at Pico A's ADC0. Electronics and winch voltages come from the INA228s (U10, U11).
CAPACITORS - 100uF 63V bulk on each 10S input; 470uF 35V on the 15 V A4988 supply (C25); 100nF ADC filters. The pack tap filter cap is C4 at Pico A's ADC0 pin; J11 is JST-VH so no signal plug can mate with it.
CONNECTORS - JST-XH for signals, JST-VH for the 10S tap (J11) and the 4S backup (J18), XT60 for the 10S inputs; J16 is female (switched output)
10S INPUTS - XT60 (pin 1 = notched end = negative, per the XT60 convention) + in-line Kelvin shunts; the sense pins have their own nets (ELEC/WINCH_SHUNT_P/N). Both packs share one 10S bus; the drive is sensed off-board: its current never crosses this carrier.
WINCH KILL PATH - high-side P-FET, fail-safe OFF, feeding the ESC on J16
DECOUPLING - 100nF per supply pin; C13 is the BNO085 internal-LDO cap (required)
RAIL BULK + STEPPER MOTOR BULK
I2C PULL-UPS - 4.7k pair on every used TCA9548A channel (a mux isolates the channels, so the upstream pair does not serve them). CH2 is free: the BMP390 (U6) came off in rev F
POD PCB - separate board, here for reference only. Tether pin 2 carries 15 V from U15 through F1; the pod makes its own 5 V.
REV C ADDITIONS (2026-09-24 review) - every part here connects through net labels
PROTECTION - 43 V TVS on both 10S rails (also a reverse-polarity crowbar that blows the pack fuse), +5V over-voltage clamp, Q1 gate clamp, tether TVS (24 V NUP2105L, D6)
SERIES RESISTORS ON EVERY OFF-BOARD SIGNAL (brief rule) - GPS UART and winch ESC PWM. The pod tether is RS-485 now (U13, see TETHER RS-485), which needs none
WS2812 LEVEL SHIFT (3.3 V Pico A -> 5 V LED data) + SENSOR STRAPS
HULL LEAK - probes on Pico A's ADC1/ADC2 (GP27/GP28), excited from GP22 only while sampling (reads fresh water, limits probe electrolysis)
BRING-UP - test points, power LEDs, WINCH ON LED, optional CAN termination (fit JP1 only if this node ends the bus)
TETHER RS-485 (2026-09-25, Pico B since 2026-10-13) - half duplex on Pico B's UART0 (TX GP16, RX GP17); GP18 drives DE and ~RE together (high = transmit); R62 holds receive mode through reset; 120R termination at this end of the tether.
TWO PICO 2s (replaced the Teensy 4.1, 2026-10-13)
Pico A (U1, next to the Pi header): control. CAN on the PIO (can2040), SBUS, winch PWM + kill, stepper, WS2812, leak probes, 12S ADC. Pico B (U14, here): sensors. TCA9548A I2C mux, GPS, pod RS-485. A UART link joins them: LINK_A2B / LINK_B2A. Both sit socketed under the carrier, each with a USB cab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
PI LINK (rev E, 2026-10-13)
Pi UART0 (GPIO14 TX / GPIO15 RX, header pins 8 / 10) to Pico A GP17 / GP16 (its UART0 RX / TX). R66 / R67 (1k) in those lines stop either end back-powering the other through its pin. Pico A's UART0 can't also take SBUS on GP1: run SBUS or this link on the PIO. Pi GPIO23 / GPIO24 (header pins 16 / 1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
10S POWER (rev F, 2026-10-14)
Two 10S 10 Ah Li-ion packs in parallel make one 10S bus (30-42 V): drives, J13 and J14. +VELEC (10S, after R32) feeds three things: the 5 V buck A2 through D12, diode-ORed with an optional 4S backup on J18 through D13 (+VLOGIC); U15, +15V for the A4988's motor supply (it tops out at 35 V) and, thro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
